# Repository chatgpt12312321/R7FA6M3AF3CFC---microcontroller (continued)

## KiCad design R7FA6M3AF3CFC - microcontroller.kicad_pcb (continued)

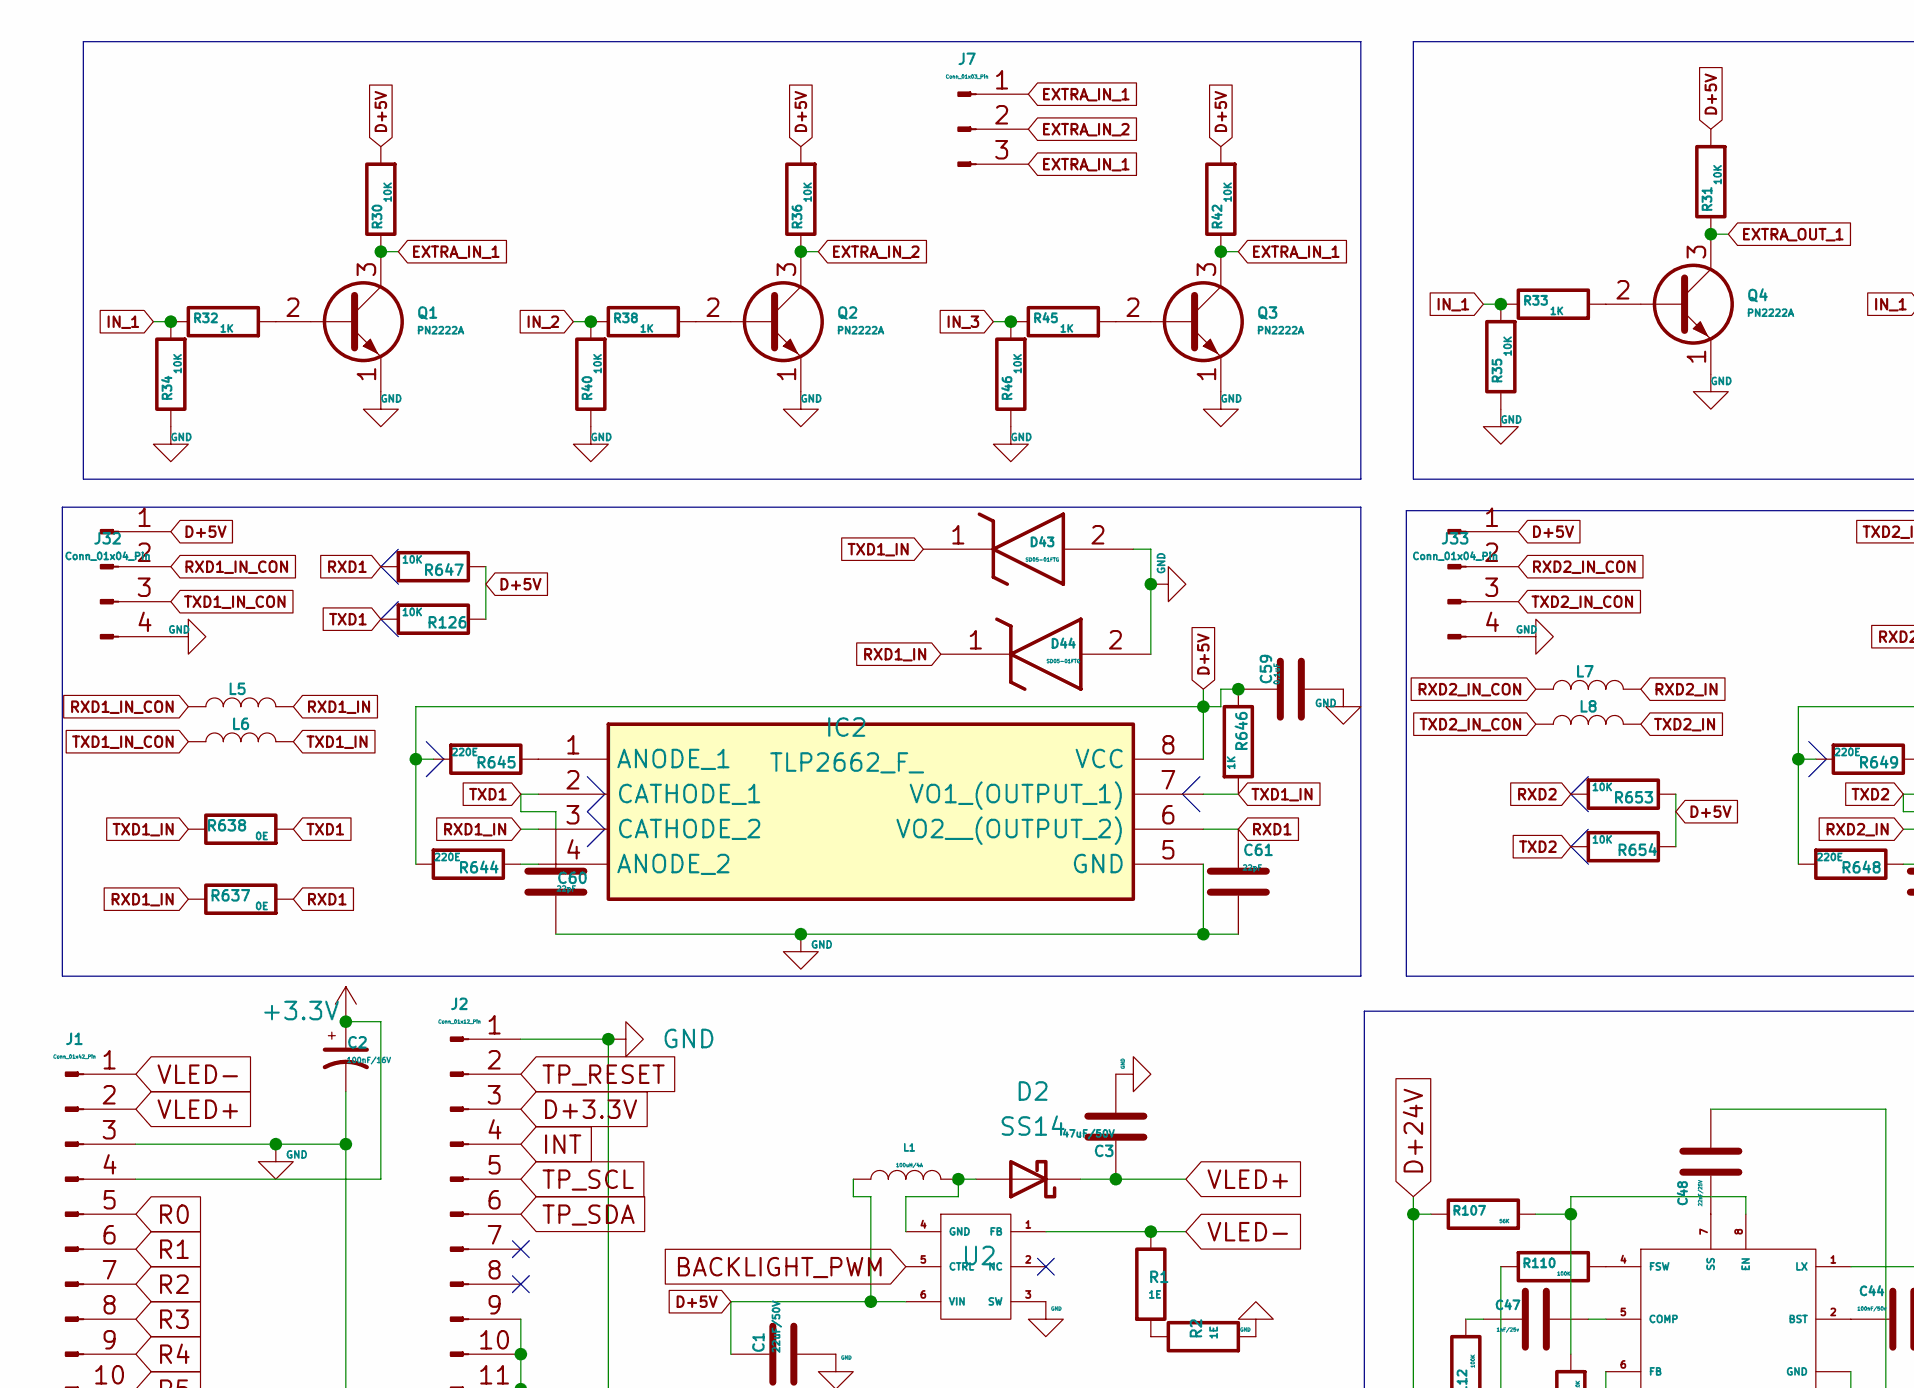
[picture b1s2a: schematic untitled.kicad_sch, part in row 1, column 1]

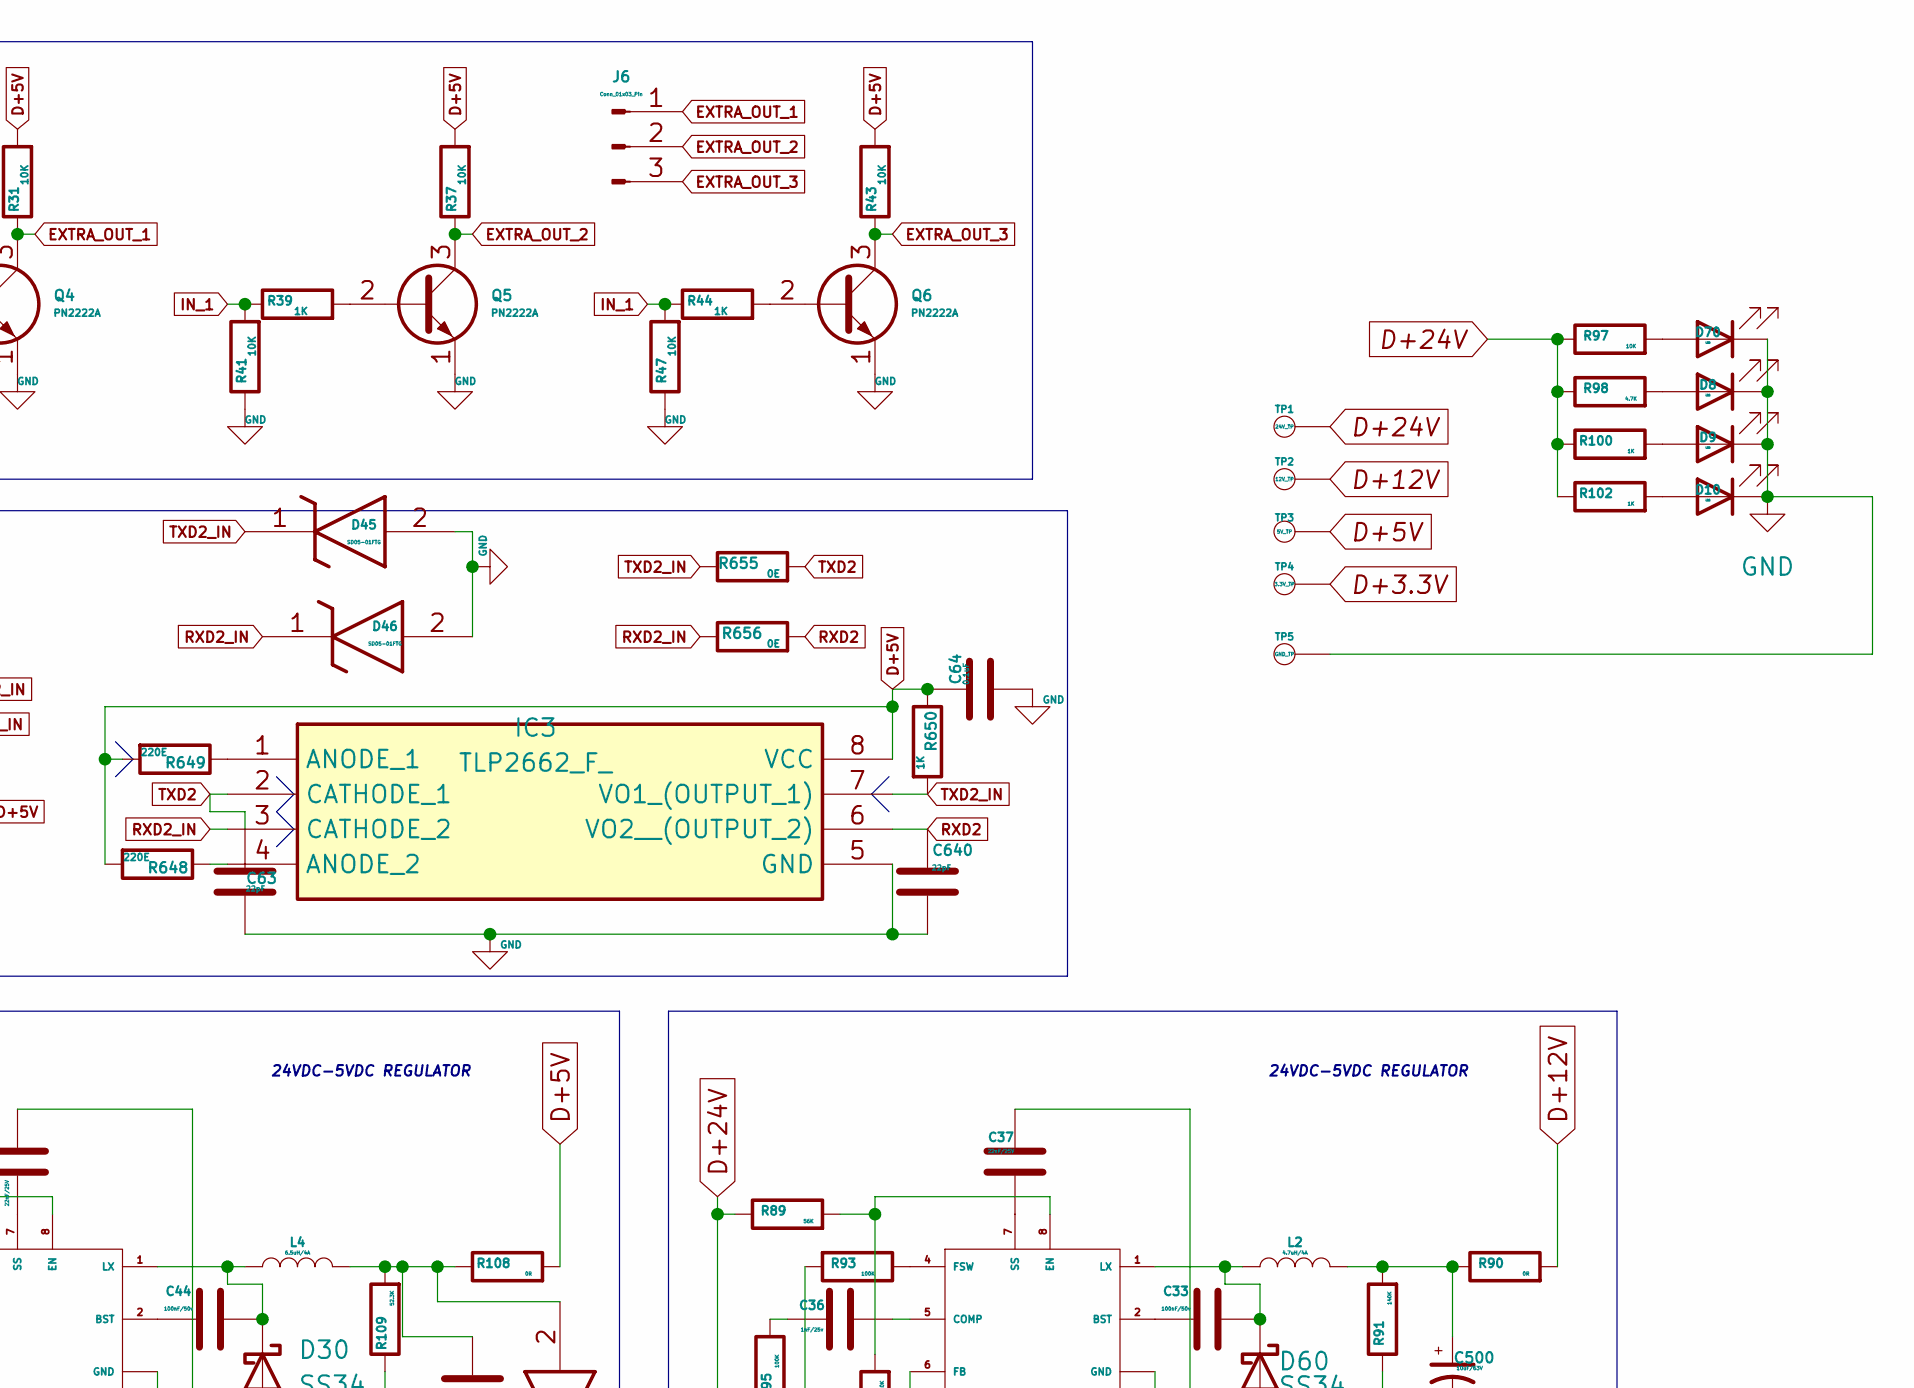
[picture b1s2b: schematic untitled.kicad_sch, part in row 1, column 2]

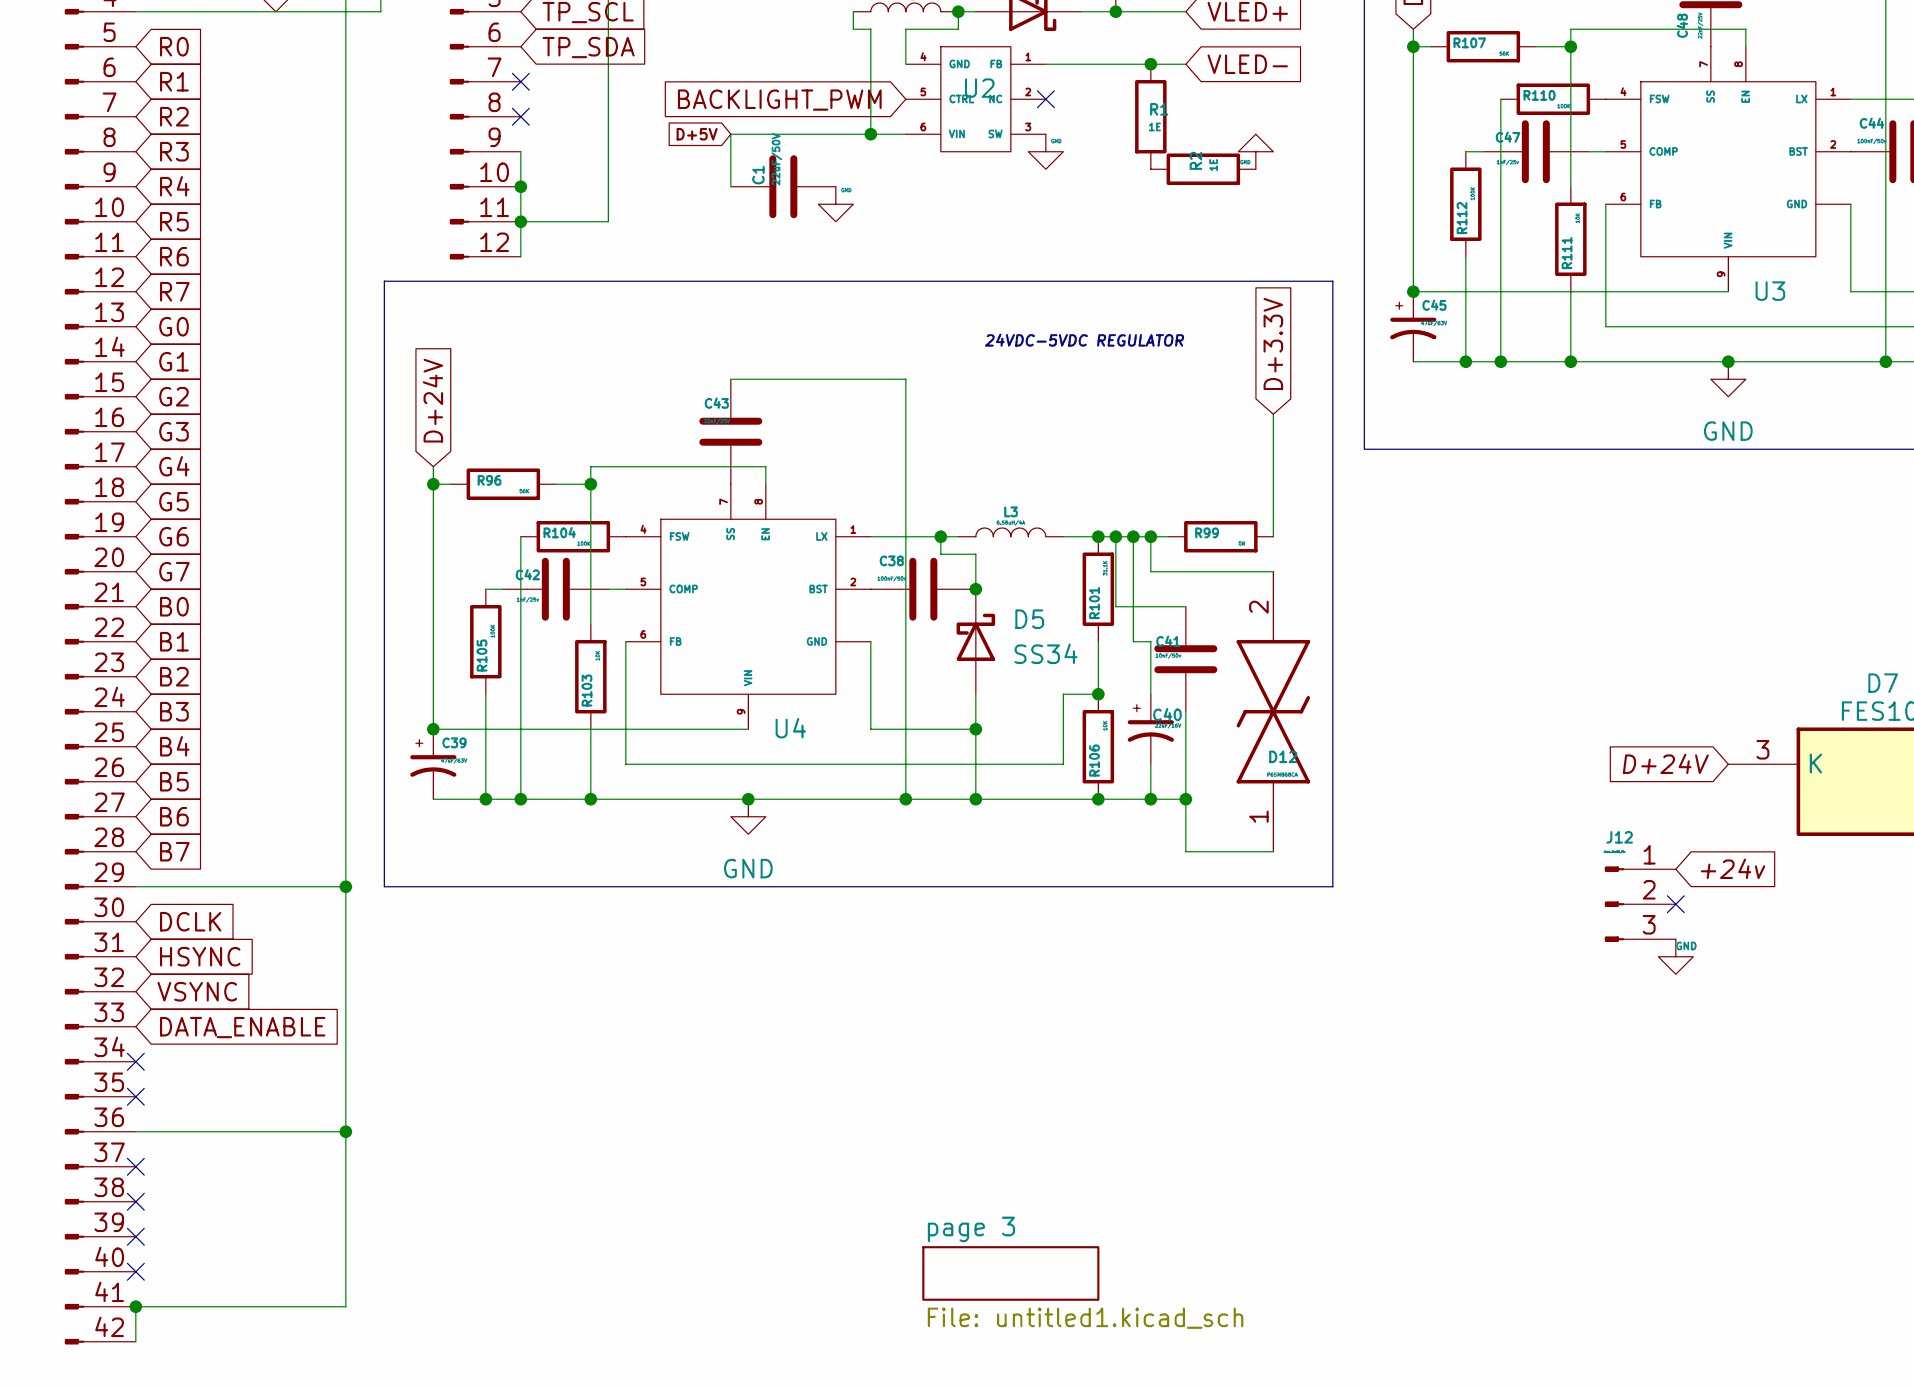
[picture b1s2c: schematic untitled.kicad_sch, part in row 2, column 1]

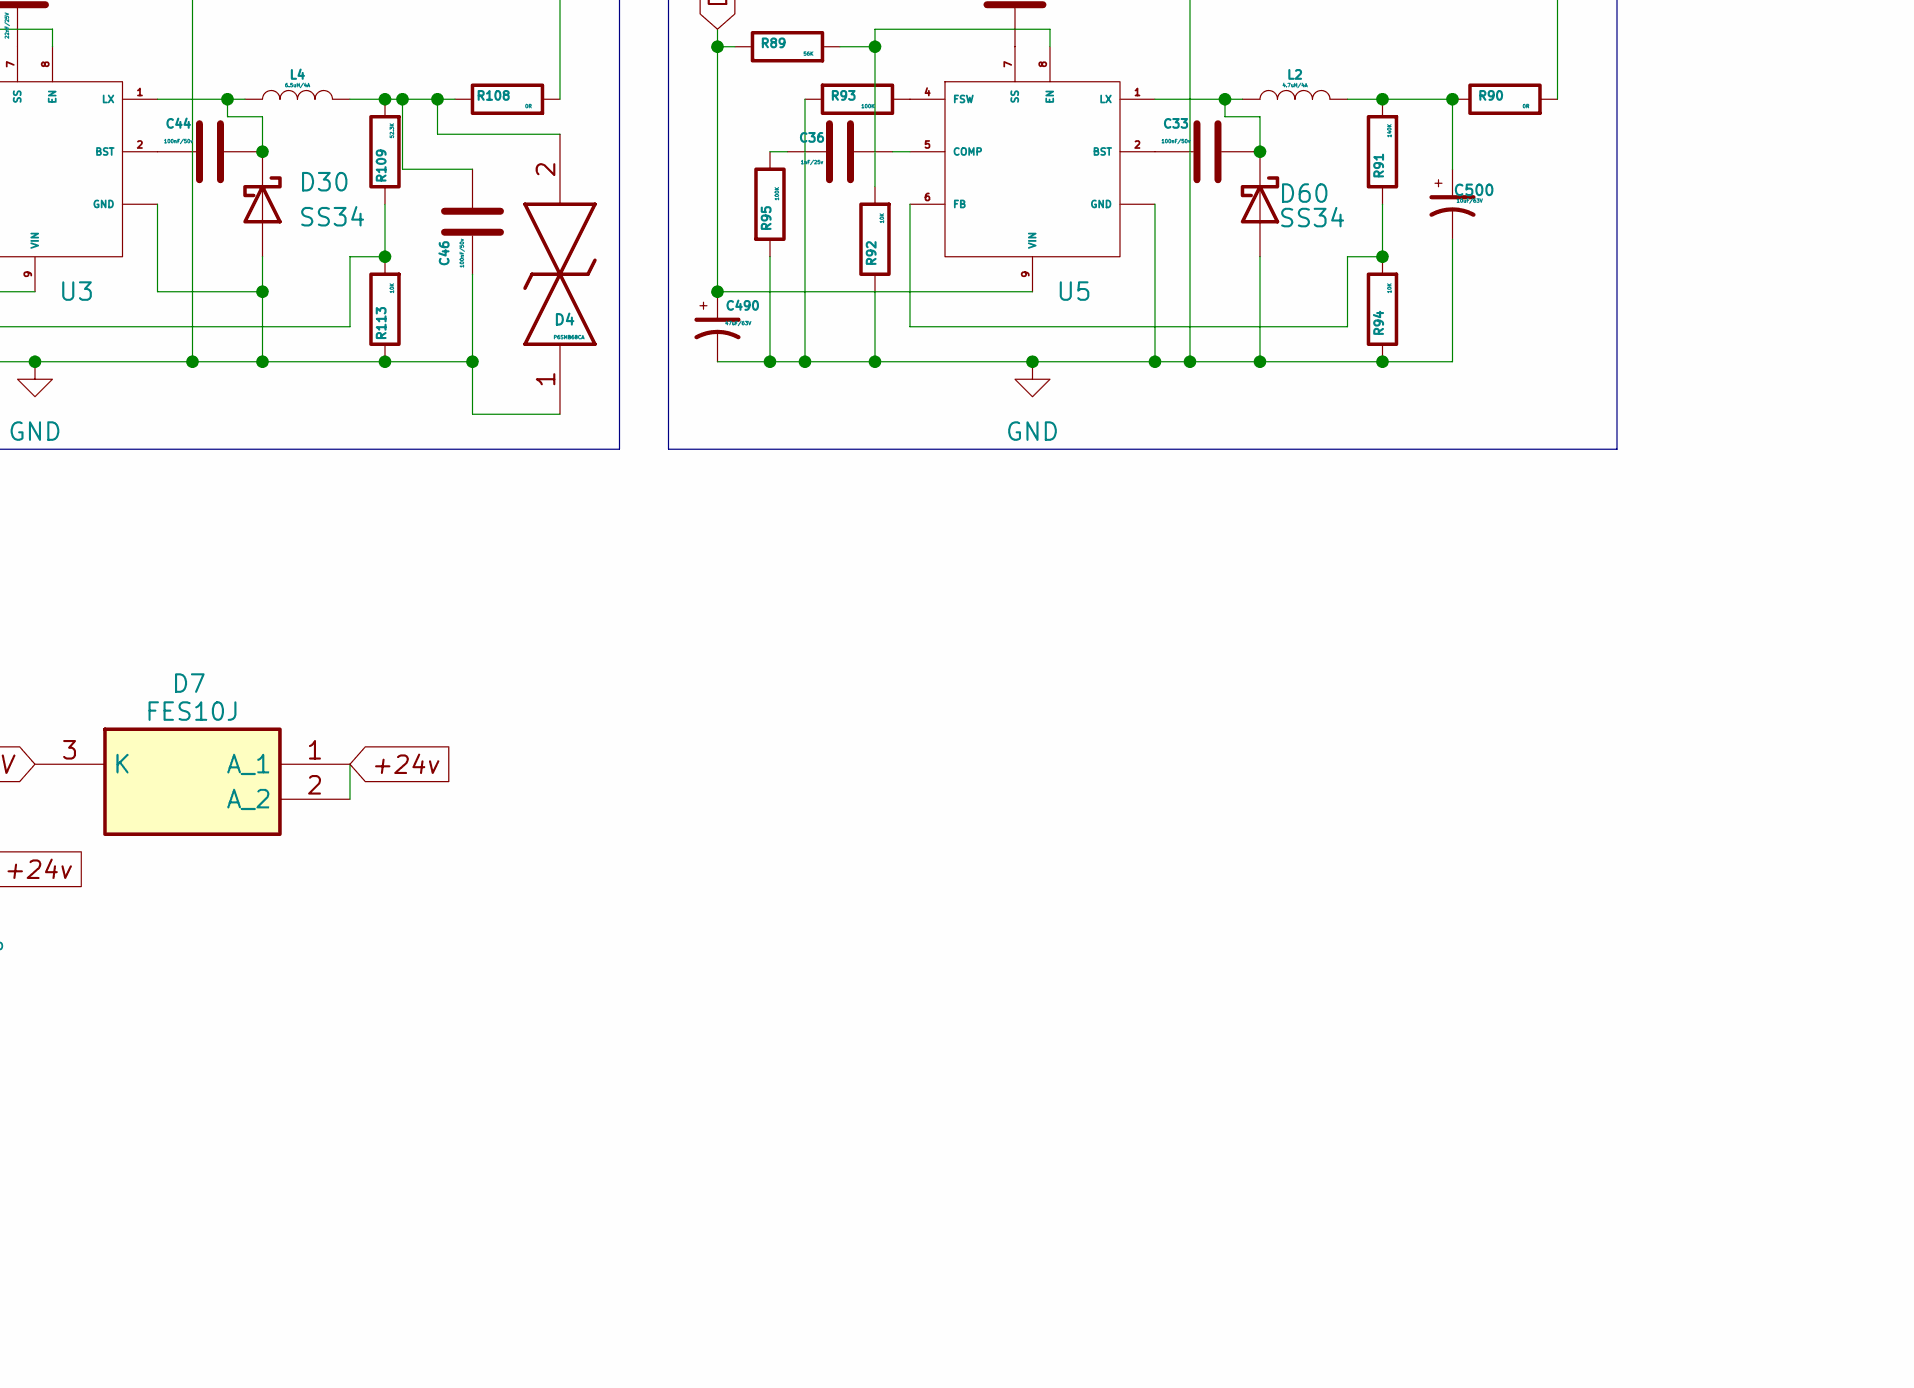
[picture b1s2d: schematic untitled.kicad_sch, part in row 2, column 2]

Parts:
C1: 22uF/50V; C_0402_1005Metric_Pad0.74x0.62mm_HandSolder
C2: 100nF/16V; C_0402_1005Metric_Pad0.74x0.62mm_HandSolder
C3: 47uF/50V; C_0402_1005Metric_Pad0.74x0.62mm_HandSolder
C33, C38, C44, C46: 100nF/50v; C_0402_1005Metric_Pad0.74x0.62mm_HandSolder
C36, C42, C47: 1nF/25v; C_0402_1005Metric_Pad0.74x0.62mm_HandSolder
C37, C43, C48: 22nF/25V; C_0402_1005Metric_Pad0.74x0.62mm_HandSolder
C39, C45, C490: 47uF/63V; C_0402_1005Metric_Pad0.74x0.62mm_HandSolder
C40: 22uF/16V; C_0402_1005Metric_Pad0.74x0.62mm_HandSolder
C41: 10nF/50v; C_0402_1005Metric_Pad0.74x0.62mm_HandSolder
C59, C64: 0.1uF; C_0402_1005Metric_Pad0.74x0.62mm_HandSolder
C60, C61, C63, C640: 22pF; C_0402_1005Metric_Pad0.74x0.62mm_HandSolder
C500: 10uF/63V; C_0402_1005Metric_Pad0.74x0.62mm_HandSolder
D2: SS14; D_SMA
D4, D12: P6SMB68CA; DIONM5436X261M; Mouser Part Number 576-P6SMB68CA
D5, D30, D60: SS34; D_SMA
D7: FES10J; FES10D; Mouser Part Number 512-FES10J
D8, D9, D10: LED; LED_0201_0603Metric
D43, D44, D45, D46: SD05-01FTG; SOD2613X114L; Mouser Part Number 576-SD05-01FTG
D70: LED; LED_0201_0603Metric_Pad0.64x0.40mm_HandSolder
IC2, IC3: TLP2662_F_; DIP762W50P254L966H390Q8N; Mouser Part Number 757-TLP2662F
J1: Conn_01x42_Pin; PinHeader_2x21_P2.54mm_Vertical_SMD
J2: Conn_01x12_Pin; PinHeader_1x12_P2.54mm_Vertical_SMD_Pin1Right
J6, J7, J12: Conn_01x03_Pin; PinHeader_1x03_P2.54mm_Vertical_SMD_Pin1Right
J32, J33: Conn_01x04_Pin; PinHeader_1x04_P2.54mm_Vertical_SMD_Pin1Right
L1: 100uH/4A; L_Axial_L5.3mm_D2.2mm_P7.62mm_Horizontal_Vishay_IM-1
L2: 4.7uH/4A; L_Axial_L5.3mm_D2.2mm_P7.62mm_Horizontal_Vishay_IM-1
L3: 6.58uH/4A; L_Axial_L5.3mm_D2.2mm_P7.62mm_Horizontal_Vishay_IM-1
L4: 6.5uH/4A; L_Axial_L5.3mm_D2.2mm_P7.62mm_Horizontal_Vishay_IM-1
L5, L6, L7, L8: L_Axial_L5.3mm_D2.2mm_P7.62mm_Horizontal_Vishay_IM-1
Q1, Q2, Q3, Q4, Q5, Q6: PN2222A; TO-92_Inline
R1, R2: 1E; R_0805_2012Metric_Pad1.20x1.40mm_HandSolder
R30, R31, R34, R35, R36, R37, R40, R41, R42, R43, R46, R47, R92, R94, R97, R103, R106, R111, R113, R126, R647, R653, R654: 10K; R_0805_2012Metric_Pad1.20x1.40mm_HandSolder
R32, R33, R38, R39, R44, R45, R100, R102, R646, R650: 1K; R_0805_2012Metric_Pad1.20x1.40mm_HandSolder
R89, R96, R107: 56K; R_0805_2012Metric_Pad1.20x1.40mm_HandSolder
R90, R99, R108: 0R; R_0805_2012Metric_Pad1.20x1.40mm_HandSolder
R91: 140K; R_0805_2012Metric_Pad1.20x1.40mm_HandSolder
R93, R95, R104, R105, R110, R112: 100K; R_0805_2012Metric_Pad1.20x1.40mm_HandSolder
R98: 4.7K; R_0805_2012Metric_Pad1.20x1.40mm_HandSolder
R101: 31.1K; R_0805_2012Metric_Pad1.20x1.40mm_HandSolder
R109: 52.3K; R_0805_2012Metric_Pad1.20x1.40mm_HandSolder
R637, R638, R655, R656: 0E; R_0805_2012Metric_Pad1.20x1.40mm_HandSolder
R644, R645, R648, R649: 220E; R_0805_2012Metric_Pad1.20x1.40mm_HandSolder
TP1: 24V_TP; TestPoint_Loop_D2.50mm_Drill1.0mm
TP2: 12V_TP; TestPoint_Loop_D1.80mm_Drill1.0mm_Beaded
TP3: 5V_TP; TestPoint_Loop_D1.80mm_Drill1.0mm_Beaded
TP4: 3.3V_TP; TestPoint_Loop_D1.80mm_Drill1.0mm_Beaded
TP5: GND_TP; TestPoint_Loop_D1.80mm_Drill1.0mm_Beaded
U2: SGM3756
U3, U4, U5: AOZ1283PI

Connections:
+3.3V: C2.1, J1.4
+24v: D7.1 (A_1), D7.2 (A_2), J12.1
B0: J1.21; also elsewhere on the board
B1: J1.22; also elsewhere on the board
B2: J1.23; also elsewhere on the board
B3: J1.24; also elsewhere on the board
B4: J1.25; also elsewhere on the board
B5: J1.26; also elsewhere on the board
B6: J1.27; also elsewhere on the board
B7: J1.28; also elsewhere on the board
BACKLIGHT_PWM: U2.5 (CTRL); also elsewhere on the board
D+3.3V: J2.3, R99.2, TP4.1; also elsewhere on the board
D+5V: C1.1, C59.1, C64.1, IC2.8 (VCC), IC3.8 (VCC), J32.1, J33.1, L1.1, R30.2, R31.2, R36.2, R37.2, R42.2, R43.2, R108.2, R126.1, R644.2, R645.2, R646.1, R647.1, R648.2, R649.2, R650.1, R653.1, R654.1, TP3.1, U2.6 (VIN); also elsewhere on the board
D+12V: R90.2, TP2.1; also elsewhere on the board
D+24V: C39.1, C45.1, C490.1, D7.3 (K), R89.1, R96.1, R97.1, R98.1, R100.1, R102.1, R107.1, TP1.1, U3.9 (VIN), U4.9 (VIN), U5.9 (VIN)
DATA_ENABLE: J1.33; also elsewhere on the board
DCLK: J1.30; also elsewhere on the board
EXTRA_IN_1: J7.1, J7.3, Q1.3 (C), Q3.3 (C), R30.1, R42.1
EXTRA_IN_2: J7.2, Q2.3 (C), R36.1
EXTRA_OUT_1: J6.1, Q4.3 (C), R31.1
EXTRA_OUT_2: J6.2, Q5.3 (C), R37.1
EXTRA_OUT_3: J6.3, Q6.3 (C), R43.1
G0: J1.13; also elsewhere on the board
G1: J1.14; also elsewhere on the board
G2: J1.15; also elsewhere on the board
G3: J1.16; also elsewhere on the board
G4: J1.17; also elsewhere on the board
G5: J1.18; also elsewhere on the board
G6: J1.19; also elsewhere on the board
G7: J1.20; also elsewhere on the board
HSYNC: J1.31; also elsewhere on the board
INT: J2.4; also elsewhere on the board
IN_1: R32.1, R33.1, R34.2, R35.2, R39.1, R41.2, R44.1, R47.2; also elsewhere on the board
IN_2: R38.1, R40.2; also elsewhere on the board
IN_3: R45.1, R46.2; also elsewhere on the board
MCU_GND: C1.2, C2.2, C3.2, C37.2, C39.2, C40.2, C41.1, C43.2, C45.2, C46.1, C48.2, C59.2, C60.2, C61.2, C63.2, C64.2, C490.2, C500.2, C640.2, D4.1, D5.2 (A), D8.1 (K), D9.1 (K), D10.1 (K), D12.1, D30.2 (A), D43.2 (A), D44.2 (A), D45.2 (A), D46.2 (A), D60.2 (A), D70.1 (K), IC2.5 (GND), IC3.5 (GND), J1.3, J1.29, J1.36, J1.41, J1.42, J2.1, J2.9, J2.10, J2.11, J2.12, J12.3, J32.4, J33.4, Q1.1 (E), Q2.1 (E), Q3.1 (E), Q4.1 (E), Q5.1 (E), Q6.1 (E), R2.2, R34.1, R35.1, R40.1, R41.1, R46.1, R47.1, R92.1, R93.2, R94.1, R95.2, R103.1, R104.2, R105.2, R106.1, R110.2, R111.1, R112.2, R113.1, TP5.1, U2.3 (SW), U3.3 (GND), U4.3 (GND), U5.3 (GND); also elsewhere on the board
unnamed: C36.2, R95.1
unnamed: C40.1, C41.2, D12.2, L3.2, R99.1, R101.2
unnamed: C42.2, R105.1
unnamed: C46.2, D4.2, L4.2, R108.1, R109.2
unnamed: C47.2, R112.1
unnamed: C500.1, L2.2, R90.1, R91.2
unnamed: D2.2 (A), L1.2, U2.4 (GND)
unnamed: C38.2, D5.1 (K), L3.1, U4.1 (LX)
unnamed: D8.2 (A), R98.2
unnamed: D9.2 (A), R100.2
unnamed: D10.2 (A), R102.2
unnamed: C44.2, D30.1 (K), L4.1, U3.1 (LX)
unnamed: C33.2, D60.1 (K), L2.1, U5.1 (LX)
unnamed: D70.2 (A), R97.2
unnamed: IC2.1 (ANODE_1), R645.1
unnamed: IC2.4 (ANODE_2), R644.1
unnamed: IC3.1 (ANODE_1), R649.1
unnamed: IC3.4 (ANODE_2), R648.1
unnamed: Q1.2 (B), R32.2
unnamed: Q2.2 (B), R38.2
unnamed: Q3.2 (B), R45.2
unnamed: Q4.2 (B), R33.2
unnamed: Q5.2 (B), R39.2
unnamed: Q6.2 (B), R44.2
unnamed: R1.2, R2.1
unnamed: C44.1, U3.2 (BST)
unnamed: C47.1, U3.5 (COMP)
unnamed: R107.2, R111.2, U3.8 (EN)
unnamed: R109.1, R113.2, U3.6 (FB)
unnamed: R110.1, U3.4 (FSW)
unnamed: C48.1, U3.7 (SS)
unnamed: C38.1, U4.2 (BST)
unnamed: C42.1, U4.5 (COMP)
unnamed: R96.2, R103.2, U4.8 (EN)
unnamed: R101.1, R106.2, U4.6 (FB)
unnamed: R104.1, U4.4 (FSW)
unnamed: C43.1, U4.7 (SS)
unnamed: C33.1, U5.2 (BST)
unnamed: C36.1, U5.5 (COMP)
unnamed: R89.2, R92.2, U5.8 (EN)
unnamed: R91.1, R94.2, U5.6 (FB)
unnamed: R93.1, U5.4 (FSW)
unnamed: C37.1, U5.7 (SS)
R0: J1.5; also elsewhere on the board
R1: J1.6; also elsewhere on the board
R2: J1.7; also elsewhere on the board
R3: J1.8; also elsewhere on the board
R4: J1.9; also elsewhere on the board
R5: J1.10; also elsewhere on the board
R6: J1.11; also elsewhere on the board
R7: J1.12; also elsewhere on the board
RXD1: C61.1, IC2.6 (VO2__(OUTPUT_2)), R637.2, R647.2; also elsewhere on the board
RXD1_IN: D44.1 (K), IC2.3 (CATHODE_2), L5.2, R637.1
RXD1_IN_CON: J32.2, L5.1
RXD2: C640.1, IC3.6 (VO2__(OUTPUT_2)), R653.2, R656.2; also elsewhere on the board
RXD2_IN: D46.1 (K), IC3.3 (CATHODE_2), L7.2, R656.1
RXD2_IN_CON: J33.2, L7.1
TP_RESET: J2.2; also elsewhere on the board
TP_SCL: J2.5; also elsewhere on the board
TP_SDA: J2.6
TXD1: C60.1, IC2.2 (CATHODE_1), R126.2, R638.2; also elsewhere on the board
TXD1_IN: D43.1 (K), IC2.7 (VO1_(OUTPUT_1)), L6.2, R638.1, R646.2
TXD1_IN_CON: J32.3, L6.1
TXD2: C63.1, IC3.2 (CATHODE_1), R654.2, R655.2; also elsewhere on the board
TXD2_IN: D45.1 (K), IC3.7 (VO1_(OUTPUT_1)), L8.2, R650.2, R655.1
TXD2_IN_CON: J33.3, L8.1
VLED+: C3.1, D2.1 (K), J1.2
VLED-: J1.1, R1.1, U2.1 (FB)
VSYNC: J1.32; also elsewhere on the board

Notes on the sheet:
24VDC-5VDC REGULATOR

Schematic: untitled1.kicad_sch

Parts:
C49, C54, C55, C56, C560: c104; C_0402_1005Metric_Pad0.74x0.62mm_HandSolder
C50, C51, C52: C104; C_0402_1005Metric_Pad0.74x0.62mm_HandSolder
C53: 10uF; C_0402_1005Metric_Pad0.74x0.62mm_HandSolder
C105: C56; C_0402_1005Metric_Pad0.74x0.62mm_HandSolder
D3, D40: 1N4007; D_DO-41_SOD81_P10.16mm_Horizontal
D6, D17: 3MM_LED; LED_D3.0mm_Clear
D11: ESD5Zxx; D_SOD-523
D21, D22, D23: PESD5Z5.0F
J4, J5, J8: Conn_01x06_Pin; PinHeader_1x06_P2.54mm_Vertical_SMD_Pin1Right
J9: Conn_01x04_Pin; PinHeader_1x04_P2.54mm_Vertical_SMD_Pin1Right
J11: Conn_01x02_Pin; PinHeader_1x02_P2.54mm_Vertical_SMD_Pin1Right
J17, J18, J27, J28, J29: Conn_01x07_Pin; PinHeader_1x07_P2.54mm_Vertical_SMD_Pin1Right
JP1: Conn_01x02_Pin; PinHeader_1x02_P2.54mm_Vertical_SMD_Pin1Right
Q7, Q8, Q9, Q10, Q11, Q12, Q13, Q14, Q15, Q16: PN2222A; TO-92_Inline
Q18, Q19: AOD2610; AOD4184
R13, R15, R17, R18, R19, R20, R122, R123, R124, R140, R144, R147, R148, R151, R153, R155, R157, R158, R159: 5.1K; R_0805_2012Metric_Pad1.20x1.40mm_HandSolder
R48, R49, R50, R51, R52, R53, R54, R55, R56, R57, R58, R59, R61, R62, R63, R64, R65, R67, R114, R115, R116, R117, R118, R119, R120, R121, R520, R630: 1K; R_0805_2012Metric_Pad1.20x1.40mm_HandSolder
R83, R84: 220E; R_0805_2012Metric_Pad1.20x1.40mm_HandSolder
R85, R86: 10K; R_0805_2012Metric_Pad1.20x1.40mm_HandSolder
R87, R88: 470E; R_0805_2012Metric_Pad1.20x1.40mm_HandSolder
R138, R145: 680E; R_0805_2012Metric_Pad1.20x1.40mm_HandSolder
R149, R150, R152, R154, R156: 3.3K; R_0805_2012Metric_Pad1.20x1.40mm_HandSolder
U6, U7: PC817; DIP-4_W7.62mm
U11: MCP3428x-xSL; SOIC-14_3.9x8.7mm_P1.27mm
U12, U13, U14, U15: mps20n0040d-s

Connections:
6569_VREF_1: J27.4, R151.2, R152.1
6569_VREF_2: J28.4, R153.2, R154.1
6569_VREF_3: J29.4, R155.2, R156.1
CH1+: R115.1, U12.3
CH1-: R118.1, U12.1, U12.6
CH2+: R119.1, U13.3
CH2-: R121.1, U13.1, U13.6
CH3+: R120.1, U14.3
CH3-: R117.1, U14.1, U14.6
CH4+: R114.1, U15.3
CH4-: R116.1, U15.1, U15.6
D+3.3V: C53.1, C54.1, R13.1, R15.1, R17.1, R18.1, R19.1, R20.1, R122.2, R123.2, R124.1, R138.1, R140.1, R145.1, R147.1, U11.6 (V_{DD}), U12.5, U13.5, U14.5, U15.5; also elsewhere on the board
D+5V: R48.2, R49.2, R50.2, R51.2, R56.2, R58.2, R62.2, R64.2, R144.1, R148.1, R151.1, R153.1, R155.1, R157.2, R158.2, R159.2, R520.2, R630.2; also elsewhere on the board
D+12V: D3.1 (K), D40.1 (K); also elsewhere on the board
DC_OUT_1: J11.1, R83.2, U6.4
DC_OUT_2: J11.2, R84.2, U7.4
DECAY0_1: J4.2; also elsewhere on the board
DECAY0_2: J5.2; also elsewhere on the board
DECAY1_1: J4.1; also elsewhere on the board
DECAY1_2: J5.1; also elsewhere on the board
DIR1: J17.2; also elsewhere on the board
DIR2: J18.2; also elsewhere on the board
ENABLE1: J17.1; also elsewhere on the board
ENABLE2: J18.1; also elsewhere on the board
LED_CNTRL_1: R53.1; also elsewhere on the board
LED_CNTRL_2: R55.1; also elsewhere on the board
LED_CNTRL_3: R54.1; also elsewhere on the board
LED_CNTRL_4: R52.1; also elsewhere on the board
LED_CNTRL_5: R57.1; also elsewhere on the board
LED_CNTRL_6: R59.1; also elsewhere on the board
LED_CNTRL_7: R65.1; also elsewhere on the board
LED_CNTRL_8: R63.1; also elsewhere on the board
LED_CNTRL_9: R61.1; also elsewhere on the board
LED_CNTRL_10: R67.1; also elsewhere on the board
LED_IN1: J8.1, Q8.3 (C), R49.1
LED_IN2: J8.2, Q10.3 (C), R51.1
LED_IN3: J8.3, Q9.3 (C), R50.1
LED_IN4: J8.4, Q7.3 (C), R48.1
LED_IN5: J8.5, Q11.3 (C), R56.1
LED_IN6: J8.6, Q12.3 (C), R58.1
LED_IN7: J9.1, Q15.3 (C), R64.1
LED_IN8: J9.2, Q14.3 (C), R62.1
LED_IN9: J9.3, Q13.3 (C), R520.1
LED_IN10: J9.4, Q16.3 (C), R630.1
M0_1: J17.6; also elsewhere on the board
M0_2: J18.6; also elsewhere on the board
M1_1: J17.4; also elsewhere on the board
M1_2: J18.4; also elsewhere on the board
MCU_GND: C53.2, C54.2, C55.2, C56.2, C105.2, C560.2, D11.2 (A), D21.2, D22.2, D23.2, J4.6, J5.6, J27.7, J28.7, J29.7, JP1.1, Q7.1 (E), Q8.1 (E), Q9.1 (E), Q10.1 (E), Q11.1 (E), Q12.1 (E), Q13.1 (E), Q14.1 (E), Q15.1 (E), Q16.1 (E), Q18.3, Q19.3, R85.1, R86.1, R149.2, R150.2, R152.2, R154.2, R156.2, U6.2, U6.3, U7.2, U7.3, U11.5 (V_{SS}), U11.9 (Adr0), U11.10 (Adr1), U12.2, U13.2, U14.2, U15.2; also elsewhere on the board
unnamed: D3.2 (A), Q18.4
unnamed: D6.2 (A), R138.2
unnamed: D17.2 (A), R145.2
unnamed: D40.2 (A), Q19.4
unnamed: Q7.2 (B), R52.2
unnamed: Q8.2 (B), R53.2
unnamed: Q9.2 (B), R54.2
unnamed: Q10.2 (B), R55.2
unnamed: Q11.2 (B), R57.2
unnamed: Q12.2 (B), R59.2
unnamed: Q13.2 (B), R61.2
unnamed: Q14.2 (B), R63.2
unnamed: Q15.2 (B), R65.2
unnamed: Q16.2 (B), R67.2
unnamed: Q18.1, R83.1, R85.2
unnamed: Q19.1, R84.1, R86.2
unnamed: R87.1, U6.1
unnamed: R88.1, U7.1
unnamed: C50.1, R115.2, U11.1 (CH1+)
unnamed: C50.2, R118.2, U11.2 (CH1-)
unnamed: C52.1, R119.2, U11.3 (CH2+)
unnamed: C52.2, R121.2, U11.4 (CH2-)
unnamed: C51.1, R120.2, U11.11 (CH3+)
unnamed: C51.2, R117.2, U11.12 (CH3-)
unnamed: C49.1, R114.2, U11.13 (CH4+)
unnamed: C49.2, R116.2, U11.14 (CH4-)
OUT+12V: J4.5, J5.5, J27.6, J28.6, J29.6
OUTPUT_1: R87.2; also elsewhere on the board
OUTPUT_2: R88.2; also elsewhere on the board
PUMP1_FWD: J27.2, R13.2; also elsewhere on the board
PUMP1_PWM: J27.1; also elsewhere on the board
PUMP1_REV: J27.3, R18.2; also elsewhere on the board
PUMP2_FWD: J28.2, R15.2; also elsewhere on the board
PUMP2_PWM: J28.1; also elsewhere on the board
PUMP2_REV: J28.3, R19.2; also elsewhere on the board
PUMP3_FWD: J29.2, R17.2; also elsewhere on the board
PUMP3_PWM: J29.1; also elsewhere on the board
PUMP3_REV: J29.3, R20.2; also elsewhere on the board
PUMP_CURRENT_SENSE_ADC1: C560.1, D21.1, J27.5, R157.1; also elsewhere on the board
PUMP_CURRENT_SENSE_ADC2: C105.1, D22.1, J28.5, R158.1; also elsewhere on the board
PUMP_CURRENT_SENSE_ADC3: C56.1, D23.1, J29.5, R159.1; also elsewhere on the board
SCL1: R122.1, U11.8 (SCL); also elsewhere on the board
SDA1: R123.1, U11.7 (SDA); also elsewhere on the board
STEP1: J17.3; also elsewhere on the board
STEP2: J18.3; also elsewhere on the board
TEMP_SENSOR_1: C55.1, D11.1 (K), JP1.2, R124.2; also elsewhere on the board
TOFF1: J17.7; also elsewhere on the board
TOFF2: J18.7; also elsewhere on the board
VREF1: J4.4, R144.2, R149.1
VREF2: J5.4, R148.2, R150.1
nFAULT_1: D6.1 (K), J4.3, R140.2; also elsewhere on the board
nFAULT_2: D17.1 (K), J5.3, R147.2; also elsewhere on the board
nSLEEP1: J17.5; also elsewhere on the board
nSLEEP2: J18.5; also elsewhere on the board

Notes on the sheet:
TO STEPPER MOTOR PCB
TO 6569 MOTOR PCB
MOSFET OUTPUTS
TEMPERATURE SENSOR
LED OUTPUTS
PRESSURE SENSOR

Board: 2 copper layers, 280 parts (0 on the bottom side), 226 nets, no tracks yet.
